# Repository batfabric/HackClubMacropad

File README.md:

# HackClubMacropad
Macropad for the hack club and amd collaboration

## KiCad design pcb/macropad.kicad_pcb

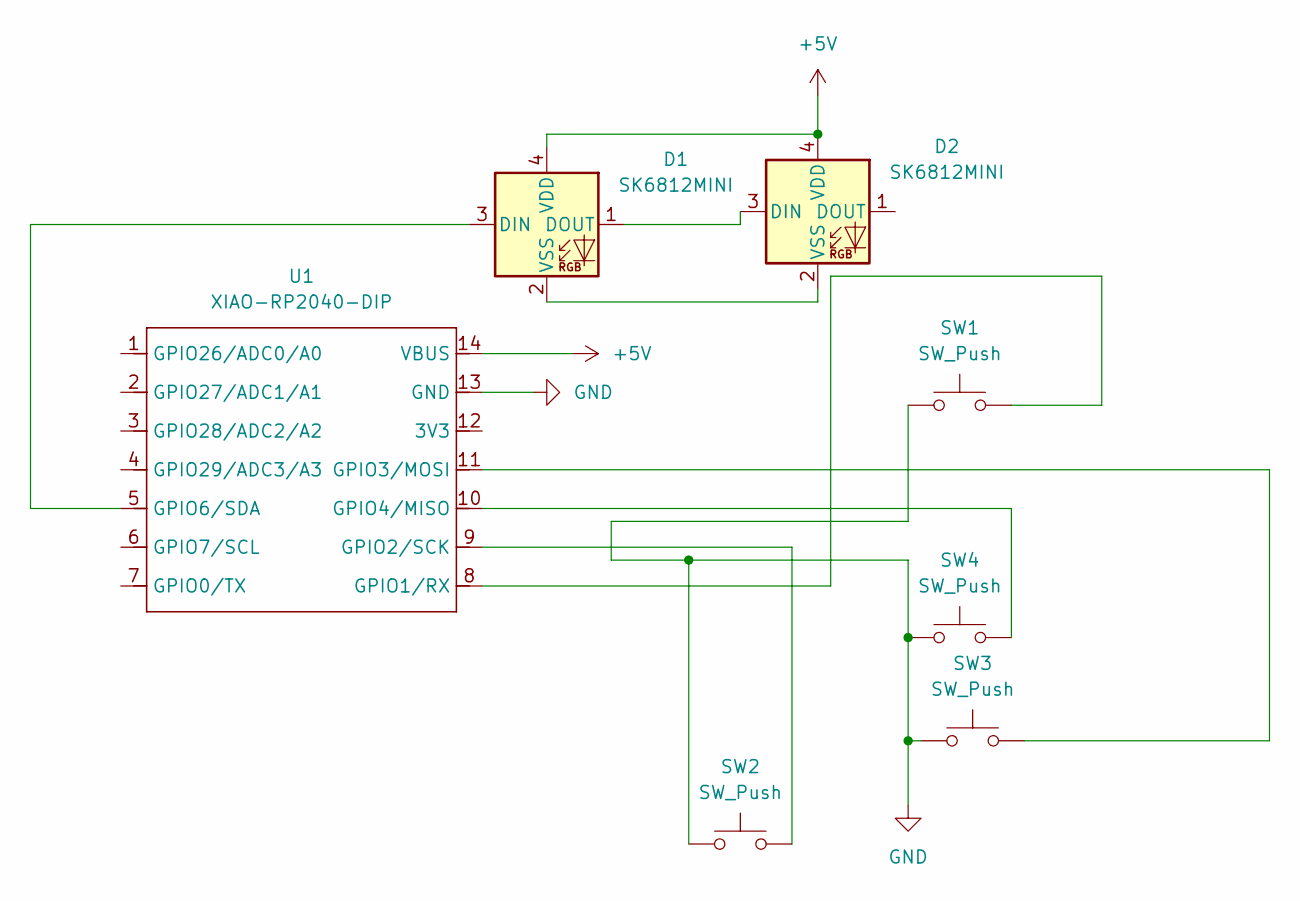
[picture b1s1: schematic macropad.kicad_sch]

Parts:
D1, D2: SK6812MINI; LED_SK6812MINI_PLCC4_3.5x3.5mm_P1.75mm
SW1, SW2, SW3, SW4: SW_Push; SW_Cherry_MX_1.00u_PCB
U1: XIAO-RP2040-DIP

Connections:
+5V: D1.4 (VDD), D2.4 (VDD), U1.14 (VBUS)
GND: SW1.1, SW2.1, SW3.1, SW4.1, U1.13 (GND)
unnamed: D1.3 (DIN), U1.5 (GPIO6/SDA)
unnamed: D1.1 (DOUT), D2.3 (DIN)
unnamed: D1.2 (VSS), D2.2 (VSS)
unnamed: SW1.2, U1.8 (GPIO1/RX)
unnamed: SW2.2, U1.9 (GPIO2/SCK)
unnamed: SW3.2, U1.11 (GPIO3/MOSI)
unnamed: SW4.2, U1.10 (GPIO4/MISO)

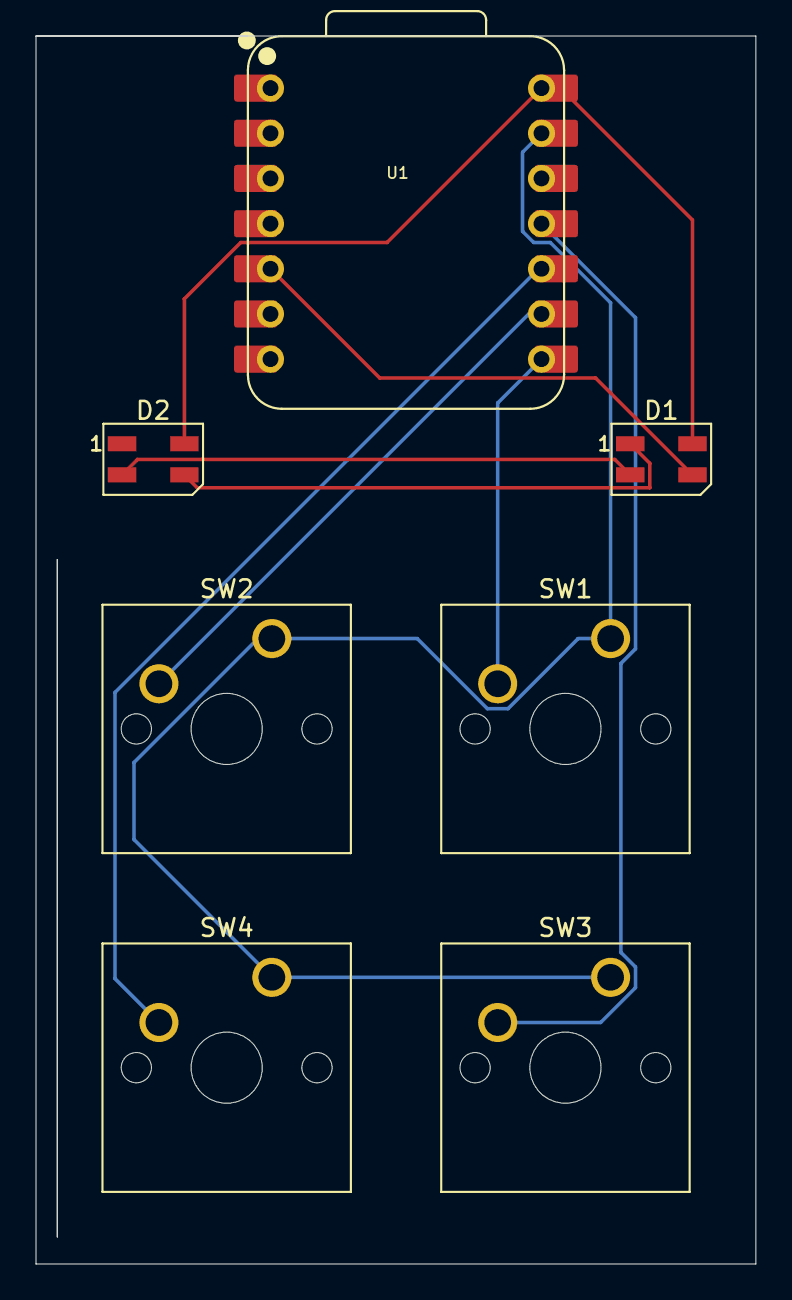
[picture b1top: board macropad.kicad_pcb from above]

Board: 2 copper layers, 40.5 x 69.1 mm, 7 parts (0 on the bottom side), 9 nets.

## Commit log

2025-12-04 Add README for the project
2025-12-06 added PCB files for the macropad
2025-12-31 Finalised PCB
